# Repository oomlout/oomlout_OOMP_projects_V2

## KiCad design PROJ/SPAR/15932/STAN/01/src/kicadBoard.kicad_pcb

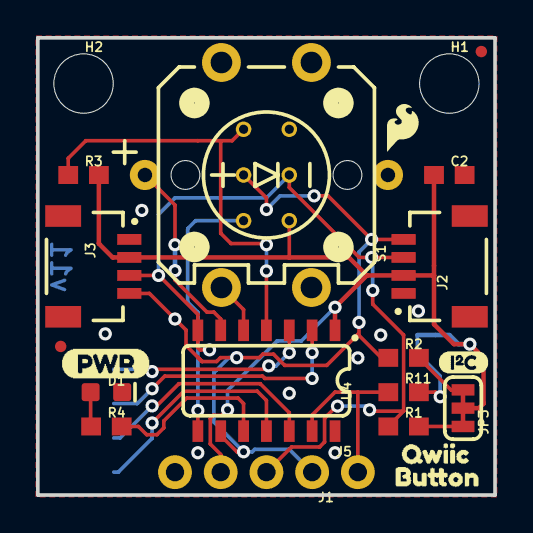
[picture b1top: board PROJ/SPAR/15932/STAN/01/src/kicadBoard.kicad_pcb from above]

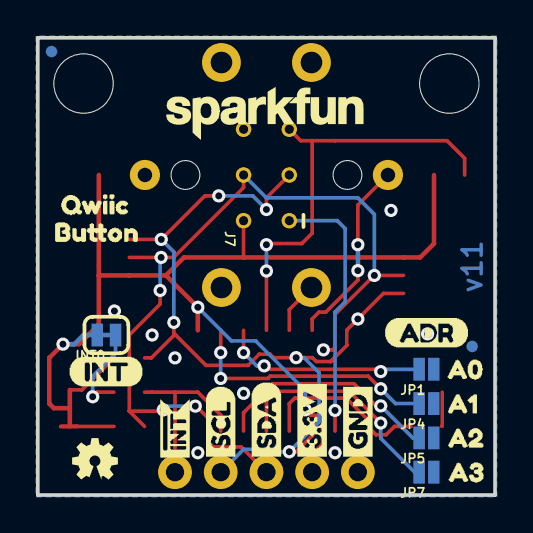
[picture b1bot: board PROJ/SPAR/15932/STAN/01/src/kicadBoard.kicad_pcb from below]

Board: 2 copper layers, 25.4 x 25.4 mm, 48 parts (23 on the bottom side), 18 nets.

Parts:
C2: 0.1uF; 0603
D1: RED; LED-0603
FRAME1: FRAME-LETTER; CREATIVE_COMMONS
H1, H2: STAND-OFF
INT0: JUMPER-SMT_2_NC_TRACE_SILK; SMT-JUMPER_2_NC_TRACE_SILK
J1: 1X04_NO_SILK
J2, J3: QWIIC_RIGHT_ANGLE; JST04_1MM_RA
J5: 1X01_NO_SILK
J7: ISP; 2X3_TEST_POINTS
JP1, JP4, JP5, JP7: JUMPER-SMT_2_NO_NO-SILK; SMT-JUMPER_2_NO_NO-SILK
JP2, JP6, JP8, JP9: FIDUCIALUFIDUCIAL; MICRO-FIDUCIAL
JP3: JUMPER-SMT_3_2-NC_TRACE_SILK; SMT-JUMPER_3_2-NC_TRACE_SILK
LOGO1: OSHW-LOGOMINI; OSHW-LOGO-MINI
LOGO2: REVISION
LOGO3: SFE_LOGO_NAME.1_INCH; SFE_LOGO_NAME_.1
LOGO4: SFE_LOGO_FLAME.1_INCH; SFE_LOGO_FLAME_.1
R1, R2: 2.2k; 0603
R3, R11: 10k; 0603
R4: 1k; 0603
S1: Button; TACTILE_SWITCH_LED_PTH_12MM
U4: ATTINY84-ARDUINO; SO14
U$1, U$2: BUTTON1
U$3: PWR-()-04
U$4: INT-()-04
U$5: SCL
U$6: SDA
U$7: 3.3V
U$8: GND
U$9: (ADR)
U$10: I_SUPER2_C-()-03
U$15: INT#-[_-04
U$16: A00
U$17: A11
U$19: A22
U$20, U$23: QWIIC0
U$21: A33

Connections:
3.3V: C2.1, INT0.2, J1.3, J2.2, J3.2, J7.2, JP3.2, R3.2, U4.1
ADR0: JP1.2, U4.3
ADR1: JP4.2, U4.2
ADR2: JP5.2, U4.12
ADR3: JP7.2, U4.11
GND: C2.2, D1.C, J1.4, J2.1, J3.1, J7.6, JP1.1, JP4.1, JP5.1, JP7.1, S1.2, S1.C, U4.14
INT_R: INT0.1, R11.2
LED: S1.A, U4.6
MISO: J7.1, U4.8
unnamed: D1.A, R4.1
SCL: J1.1, J2.4, J3.4, J7.3, R2.1, U4.9
SCL_PU1: JP3.1, R2.2
SDA: J1.2, J2.3, J3.3, J7.4, R1.1, U4.7
SDA_PU1: JP3.3, R1.2
STAT: R4.2, U4.10
SWITCH: S1.4, U4.5
~INT: J5.1, R11.1, U4.13
~RST: J7.5, R3.1, U4.4

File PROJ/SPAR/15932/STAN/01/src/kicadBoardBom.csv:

"Id";"Designator";"Package";"Quantity";"Designation";"Supplier and ref";
1;"H2,H1";"STAND-OFF";2;"STAND-OFF";;;
2;"D1";"LED-0603";1;"RED";;;
3;"J2,J3";"JST04_1MM_RA";2;"QWIIC_RIGHT_ANGLE";;;
4;"R4";"0603";1;"1k";;;
5;"U4";"SO14";1;"ATTINY84-ARDUINO";;;
6;"FRAME1";"CREATIVE_COMMONS";1;"FRAME-LETTER";;;
7;"R1,R2";"0603";2;"2.2k";;;
8;"R3,R11";"0603";2;"10k";;;
9;"J1";"1X04_NO_SILK";1;"";;;
10;"LOGO4";"SFE_LOGO_FLAME_.1";1;"SFE_LOGO_FLAME.1_INCH";;;
11;"U$23,U$20";"QWIIC0";2;"";;;
12;"U$1,U$2";"BUTTON1";2;"";;;
13;"U$3";"PWR-()-04";1;"";;;
14;"J5";"1X01_NO_SILK";1;"";;;
15;"JP9,JP8,JP2,JP6";"MICRO-FIDUCIAL";4;"FIDUCIALUFIDUCIAL";;;
16;"U$10";"I_SUPER2_C-()-03";1;"";;;
17;"C2";"0603";1;"0.1uF";;;
18;"S1";"TACTILE_SWITCH_LED_PTH_12MM";1;"Button";;;
19;"LOGO2";"REVISION";1;"REVISION";;;
20;"JP3";"SMT-JUMPER_3_2-NC_TRACE_SILK";1;"JUMPER-SMT_3_2-NC_TRACE_SILK";;;
21;"U$21";"A33";1;"";;;
22;"JP5,JP7,JP1,JP4";"SMT-JUMPER_2_NO_NO-SILK";4;"JUMPER-SMT_2_NO_NO-SILK";;;
23;"U$16";"A00";1;"";;;
24;"U$8";"GND";1;"";;;
25;"U$9";"(ADR)";1;"";;;
26;"J7";"2X3_TEST_POINTS";1;"ISP";;;
27;"U$6";"SDA";1;"";;;
28;"INT0";"SMT-JUMPER_2_NC_TRACE_SILK";1;"JUMPER-SMT_2_NC_TRACE_SILK";;;
29;"U$19";"A22";1;"";;;
30;"U$5";"SCL";1;"";;;
31;"LOGO1";"OSHW-LOGO-MINI";1;"OSHW-LOGOMINI";;;
32;"U$15";"INT#-[_-04";1;"";;;
33;"U$4";"INT-()-04";1;"";;;
34;"U$7";"3.3V";1;"";;;
35;"U$17";"A11";1;"";;;
36;"LOGO3";"SFE_LOGO_NAME_.1";1;"SFE_LOGO_NAME.1_INCH";;;

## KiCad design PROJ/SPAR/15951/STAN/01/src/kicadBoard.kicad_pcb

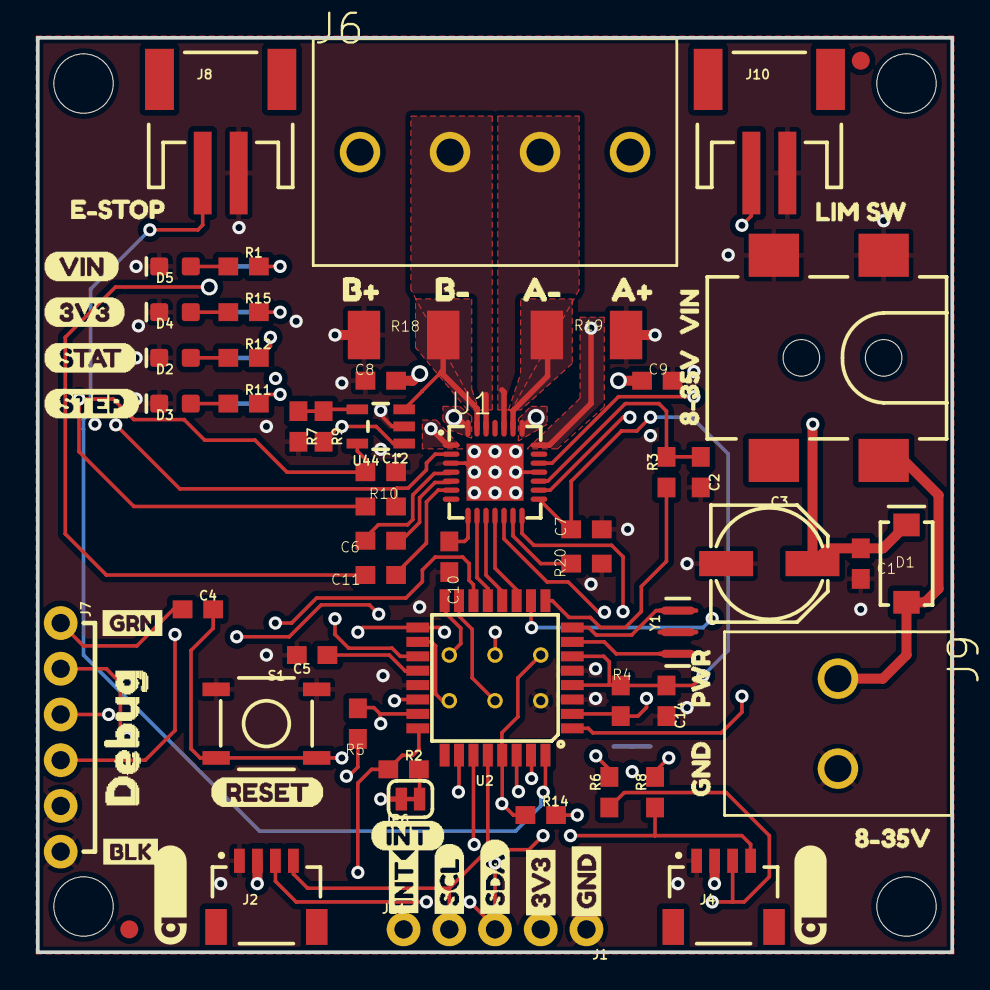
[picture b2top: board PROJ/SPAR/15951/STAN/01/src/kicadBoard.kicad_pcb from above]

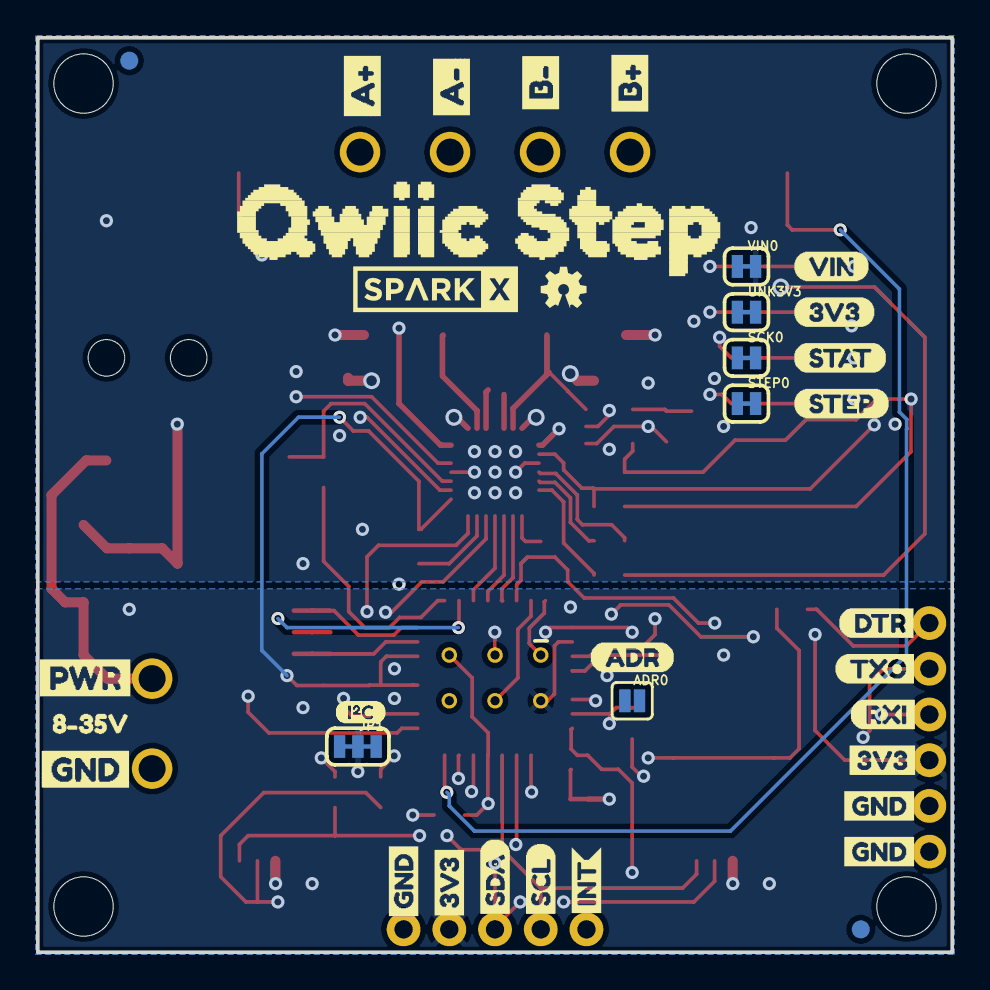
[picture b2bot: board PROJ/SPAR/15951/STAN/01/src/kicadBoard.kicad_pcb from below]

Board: 4 copper layers, 50.8 x 50.8 mm, 122 parts (37 on the bottom side), 54 nets.

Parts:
ADR0: ADR; SMT-JUMPER_2_NO_SILK
C1, C4, C5, C6, C7, C8, C9, C11, C12, C14: 0.1uF; 0603
C2: 1.0uF; 0603
C3: 47uF; PANASONIC_D
C10: 0.22uF; 0603
D1: 3A/40V/500mV; SMA-DIODE
D2: BLUE; LED-0603
D3: GREEN; LED-0603
D4: RED; LED-0603
D5: Yellow; LED-0603
FD1, FD2, FD3, FD4: FIDUCIAL1X2; FIDUCIAL-1X2
FRAME2: FRAME-LEDGER; CREATIVE_COMMONS
J1: PTH; 1X04_NO_SILK
J2, J4: Qwiic Right Angle; JST04_1MM_RA
J3: 5.5x2.1mm Barrel; POWER_JACK_SMD
J5: ISP; 2X3_TEST_POINTS
J6: LATCHTERMINAL-5MM-4
J7: 1X06_NO_SILK
J8, J10: JST-2-SMD
J9: LATCHTERMINAL-5MM-2
J11: 1X01_NO_SILK
JP1: SMT-JUMPER_3_2-NC_TRACE_SILK
JP6: INT; SMT-JUMPER_2_NC_TRACE_SILK
JP7, JP8, JP9, JP10: STAND-OFF
LOGO1: OSHW-LOGOMINI; OSHW-LOGO-MINI
R1, R2, R14: 10k; 0603
R3: 100k; 0603
R4, R5, R10, R20: 20k; 0603
R6, R8: 2.2k; 0603
R7, R15: 1k; 0603
R9: 22k; 0603
R11: 0; 0603
R12: 470; 0603
R18, R19: 0.11; 2010
S1: Tall Switch; TACTILE_SWITCH_SMD_5.2MM
SCK0: JUMPER-SMT_2_NC_TRACE_SILK; SMT-JUMPER_2_NC_TRACE_SILK
STEP0: JUMPER-SMT_2_NC_TRACE_SILK; SMT-JUMPER_2_NC_TRACE_SILK
U1: A4988ALT1; QFN-28-5MM
U2: ATMEGA328P_TQFP; TQFP32-08
U44: OPA344; SOT23-5
U$1: 3V30
U$2: 3V37
U$3: GND8
U$4: STAT5
U$5: SCL5
U$6: SDA6
U$7: STEP4
U$8: VIN3
U$9, U$29: QWIIC_5.5MM
U$10, U$11, U$40: 8#35V0
U$12: VIN1
U$13: STAT0
U$14: E#STOP2
U$15, U$16: I_SUPER2_C-()-03
U$17, U$45: 3V31
U$18: DTR4
U$19: DEBUG0
U$20: BLK2
U$21, U$22, U$44: GND0
U$23: LIM_SW3
U$24, U$30: INT4
U$25: ADR0
U$26: 3V35
U$27: RESET1
U$28: GRN1
U$31: GND6
U$32, U$54: A#2
U$33: SDA4
U$34: SCL3
U$35: RXI3
U$36, U$55: A#3
U$37: STEP2
U$38: VIN0
U$41: INT2
U$42: GND1
U$43: PWR0
U$46, U$57: B#4
U$47, U$58: B#5
U$48: TXO2
U$49: SPARKX-LOGO4; SPARKX-MEDIUM
U$53: PWR1
U$56: QWIIC_STEP0
UNK3V3: JUMPER-SMT_2_NC_TRACE_SILK; SMT-JUMPER_2_NC_TRACE_SILK
VIN0: JUMPER-SMT_2_NC_TRACE_SILK; SMT-JUMPER_2_NC_TRACE_SILK
Y1: 16MHz; RESONATOR-SMD-3.2X1.3

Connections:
3.3V: C7.1, C12.1, C14.1, J1.2, J2.2, J4.2, J5.2, J7.4, JP1.2, JP6.2, R4.2, R5.2, R10.2, R14.2, U1.15, U2.4, U2.6, U2.18, U44.5, UNK3V3.2
A49885_~RESET: R5.1, U1.12, U2.23
AMP_CUR_SENSE: R9.2, U2.19, U44.1
AREF: C5.1, U2.20
COILA+: J6.P$4, U1.21
COILA-: J6.P$3, U1.24
COILB+: J6.P$1, U1.1
COILB-: J6.P$2, U1.26
CURRENT_SENSE: R18.2, U1.27, U44.3
CUR_REF: C2.1, R3.2, U1.17
CUR_REF_PWM: R3.1, U2.9
DIR: U1.19, U2.10
DTR: C4.1, J7.1
GND: ADR0.2, C1.2, C2.2, C3.-, C5.2, C7.2, C8.2, C9.2, C10.2, C12.2, C14.2, D2.C, D3.C, D4.C, D5.C, J1.1, J2.1, J3.GND, J3.P$4, J4.1, J5.6, J7.5, J7.6, J8.2, J9.P$2, J10.2, R7.2, R18.1, R19.1, R20.2, S1.1, S1.2, U1.3, U1.18, U1.29, U2.3, U2.5, U2.21, U44.2, Y1.2
INT: J11.1, R2.1, U2.24
INT0: J8.1, U2.32
INT1: J10.1, U2.1
MISO: J5.1, U2.16
MOSI: J5.4, U2.15
MS1: U1.9, U2.13
MS2: U1.10, U2.12
MS3: U1.11, U2.11
unnamed: D3.A, R11.1
unnamed: R7.1, R9.1, U44.4
unnamed: R19.2, U1.23
unnamed: R1.2, VIN0.1
unnamed: JP6.1, R2.2
unnamed: ADR0.1, U2.22
unnamed: D1.A, J3.VIN0, J9.P$1
unnamed: C6.1, U1.4
unnamed: C6.2, U1.5
unnamed: D5.A, R1.1
unnamed: R11.2, STEP0.1
unnamed: D2.A, R12.1
unnamed: U2.7, Y1.1
unnamed: U2.8, Y1.3
unnamed: JP1.3, R6.2
unnamed: JP1.1, R8.2
unnamed: R12.2, SCK0.1
unnamed: R20.1, U1.13
unnamed: C10.1, U1.8
unnamed: C11.1, U1.6
unnamed: D4.A, R15.1
unnamed: R15.2, UNK3V3.1
RXI: J7.3, U2.30
SCK: J5.3, SCK0.2, U2.17
SCL: J1.4, J2.4, J4.4, R8.1, U2.28
SDA: J1.3, J2.3, J4.3, R6.1, U2.27
STEP: STEP0.2, U1.16, U2.26
TXO: J7.2, U2.31
VIN: C1.1, C3.+, C8.1, C9.1, C11.2, D1.C, U1.22, U1.28, VIN0.2
~ENABLE: R10.1, U1.2, U2.14
~RST: C4.2, J5.5, R14.1, S1.3, S1.4, U2.29
~SLEEP: R4.1, U1.14, U2.2

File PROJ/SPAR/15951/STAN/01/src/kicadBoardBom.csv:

"Id";"Designator";"Package";"Quantity";"Designation";"Supplier and ref";
1;"J9";"LATCHTERMINAL-5MM-2";1;"";;;
2;"U$46,U$57";"B#4";2;"";;;
3;"C7,C11,C5,C1,C12,C4,C8,C6,C9,C14";"0603";10;"0.1uF";;;
4;"U$8";"VIN3";1;"";;;
5;"R3";"0603";1;"100k";;;
6;"U$9,U$29";"QWIIC_5.5MM";2;"";;;
7;"R19,R18";"2010";2;"0.11";;;
8;"D3";"LED-0603";1;"GREEN";;;
9;"C2";"0603";1;"1.0uF";;;
10;"U$40,U$10,U$11";"8#35V0";3;"";;;
11;"R5,R4,R10,R20";"0603";4;"20k";;;
12;"FD4,FD1,FD3,FD2";"FIDUCIAL-1X2";4;"FIDUCIAL1X2";;;
13;"J8,J10";"JST-2-SMD";2;"";;;
14;"J6";"LATCHTERMINAL-5MM-4";1;"";;;
15;"R15,R7";"0603";2;"1k";;;
16;"U$7";"STEP4";1;"";;;
17;"U44";"SOT23-5";1;"OPA344";;;
18;"U$28";"GRN1";1;"";;;
19;"D4";"LED-0603";1;"RED";;;
20;"U$23";"LIM_SW3";1;"";;;
21;"U$24,U$30";"INT4";2;"";;;
22;"J11";"1X01_NO_SILK";1;"";;;
23;"J2,J4";"JST04_1MM_RA";2;"Qwiic Right Angle";;;
24;"U$14";"E#STOP2";1;"";;;
25;"D2";"LED-0603";1;"BLUE";;;
26;"D1";"SMA-DIODE";1;"3A/40V/500mV";;;
27;"U$32,U$54";"A#2";2;"";;;
28;"JP7,JP8,JP10,JP9";"STAND-OFF";4;"STAND-OFF";;;
29;"R11";"0603";1;"0";;;
30;"R14,R1,R2";"0603";3;"10k";;;
31;"U$19";"DEBUG0";1;"";;;
32;"U$47,U$58";"B#5";2;"";;;
33;"U$2";"3V37";1;"";;;
34;"U$42";"GND1";1;"";;;
35;"U1";"QFN-28-5MM";1;"A4988ALT1";;;
36;"U2";"TQFP32-08";1;"ATMEGA328P_TQFP";;;
37;"R6,R8";"0603";2;"2.2k";;;
38;"R9";"0603";1;"22k";;;
39;"U$12";"VIN1";1;"";;;
40;"C3";"PANASONIC_D";1;"47uF";;;
41;"U$4";"STAT5";1;"";;;
42;"U$43";"PWR0";1;"";;;
43;"J1";"1X04_NO_SILK";1;"PTH";;;
44;"C10";"0603";1;"0.22uF";;;
45;"U$1";"3V30";1;"";;;
46;"R12";"0603";1;"470";;;
47;"JP6";"SMT-JUMPER_2_NC_TRACE_SILK";1;"INT";;;
48;"U$36,U$55";"A#3";2;"";;;
49;"FRAME2";"CREATIVE_COMMONS";1;"FRAME-LEDGER";;;
50;"U$20";"BLK2";1;"";;;
51;"U$6";"SDA6";1;"";;;
52;"S1";"TACTILE_SWITCH_SMD_5.2MM";1;"Tall Switch";;;
53;"J3";"POWER_JACK_SMD";1;"5.5x2.1mm Barrel";;;
54;"Y1";"RESONATOR-SMD-3.2X1.3";1;"16MHz";;;
55;"U$5";"SCL5";1;"";;;
56;"U$3";"GND8";1;"";;;
57;"U$41";"INT2";1;"";;;
58;"J7";"1X06_NO_SILK";1;"";;;
59;"U$27";"RESET1";1;"";;;
60;"D5";"LED-0603";1;"Yellow";;;
61;"U$25";"ADR0";1;"";;;
62;"JP1";"SMT-JUMPER_3_2-NC_TRACE_SILK";1;"";;;
63;"SCK0,STEP0,VIN0,UNK3V3";"SMT-JUMPER_2_NC_TRACE_SILK";4;"JUMPER-SMT_2_NC_TRACE_SILK";;;
64;"U$38";"VIN0";1;"";;;
65;"U$13";"STAT0";1;"";;;
66;"U$18";"DTR4";1;"";;;
67;"U$45,U$17";"3V31";2;"";;;
68;"U$31";"GND6";1;"";;;
69;"U$26";"3V35";1;"";;;
70;"ADR0";"SMT-JUMPER_2_NO_SILK";1;"ADR";;;
71;"U$56";"QWIIC_STEP0";1;"";;;
72;"U$44,U$22,U$21";"GND0";3;"";;;
73;"U$48";"TXO2";1;"";;;
74;"U$49";"SPARKX-MEDIUM";1;"SPARKX-LOGO4";;;
75;"U$37";"STEP2";1;"";;;
76;"U$35";"RXI3";1;"";;;
77;"U$34";"SCL3";1;"";;;
78;"U$33";"SDA4";1;"";;;
79;"U$16,U$15";"I_SUPER2_C-()-03";2;"";;;
80;"LOGO1";"OSHW-LOGO-MINI";1;"OSHW-LOGOMINI";;;
81;"U$53";"PWR1";1;"";;;
82;"J5";"2X3_TEST_POINTS";1;"ISP";;;

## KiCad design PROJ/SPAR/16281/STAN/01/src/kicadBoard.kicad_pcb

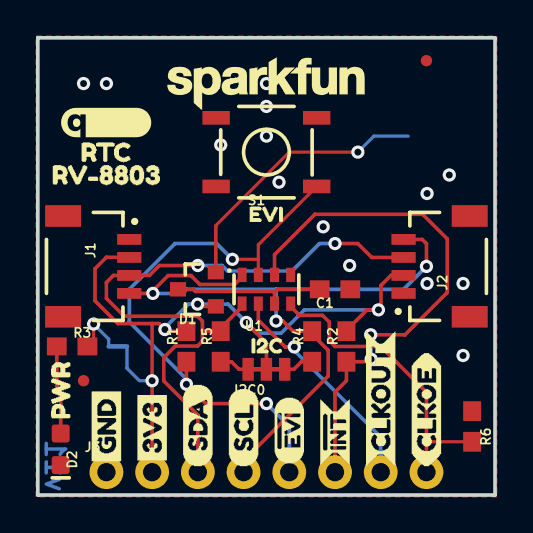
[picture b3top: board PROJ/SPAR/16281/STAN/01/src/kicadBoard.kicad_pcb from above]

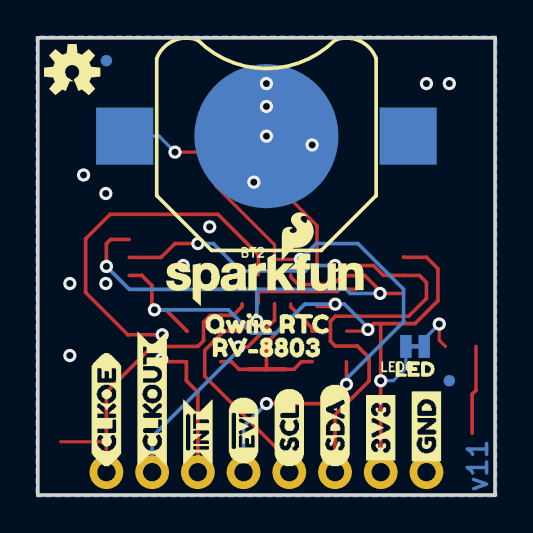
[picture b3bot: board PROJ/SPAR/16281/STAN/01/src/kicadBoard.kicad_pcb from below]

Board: 2 copper layers, 25.4 x 25.4 mm, 50 parts (17 on the bottom side), 14 nets.

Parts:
BT2: BATTCON_12MM
C1: 10nF; 0603
D1: BAS70-05; SOT23-3
D2: RED; LED-0603
FD1, FD2, FD3, FD4: FIDUCIALUFIDUCIAL; FIDUCIAL-MICRO
FRAME1: FRAME-LETTER; CREATIVE_COMMONS
I2C0: JUMPER-SMT_3_2-NC_TRACE_NO-SILK; SMT-JUMPER_3_2-NC_TRACE_NO-SILK
J1, J2: QWIIC; JST04_1MM_RA
J3: 1X08_NO_SILK
LED0: JUMPER-SMT_2_NC_TRACE_NO-SILK; SMT-JUMPER_2_NC_TRACE_NO-SILK
LOGO1: SFE_LOGO_NAME_FLAME.1_INCH; SFE_LOGO_NAME_FLAME_.1
LOGO2: OSHW-LOGOS; OSHW-LOGO-S
LOGO4: QWIIC_LOGO_5MM; QWIIC_5MM
LOGO5: SFE_LOGO_NAME.1_INCH; SFE_LOGO_NAME_.1
R1, R2, R6: 100k; 0603
R3: 1k; 0603
R4, R5: 4.7k; 0603
S1: MOMENTARY-SWITCH-SPST-SMD-5.2MM-TALL; TACTILE_SWITCH_SMD_5.2MM
U1: RV-8803; RV-3028
U$1, U$2: 3V31
U$3, U$4: GND0
U$5, U$6: SDA2
U$7, U$8: SCL3
U$9, U$10: #EVI2
U$11, U$12: CLKOUT6
U$13, U$14: CLKOE7
U$15, U$16: #INT5
U$17: PWR7
U$18: EVI1
U$19: I2C0
U$20: LED2
U$21: QWIIC_RTC0
U$22, U$24: _RV#88031
U$25: RTC0

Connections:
3.3V: D1.1, I2C0.2, J1.2, J2.2, J3.2, LED0.2, R1.2, R2.2
CLKOE: J3.8, R6.2, U1.4
CLKOUT: J3.7, U1.2
GND: BT2.GND, C1.1, D2.C, J1.1, J2.1, J3.1, R6.1, S1.3, U1.5
unnamed: C1.2, D1.3, U1.3
unnamed: D2.A, R3.1
unnamed: BT2.PWR@1, D1.2
unnamed: LED0.1, R3.2
unnamed: I2C0.3, R5.1
unnamed: I2C0.1, R4.1
SCL: J1.4, J2.4, J3.4, R4.2, U1.8
SDA: J1.3, J2.3, J3.3, R5.2, U1.1
~EVI: J3.5, R1.1, S1.1, U1.7
~INT: J3.6, R2.1, U1.6

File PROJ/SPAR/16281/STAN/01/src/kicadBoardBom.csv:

"Id";"Designator";"Package";"Quantity";"Designation";"Supplier and ref";
1;"U$7,U$8";"SCL3";2;"";;;
2;"U$17";"PWR7";1;"";;;
3;"S1";"TACTILE_SWITCH_SMD_5.2MM";1;"MOMENTARY-SWITCH-SPST-SMD-5.2MM-TALL";;;
4;"R5,R4";"0603";2;"4.7k";;;
5;"C1";"0603";1;"10nF";;;
6;"D1";"SOT23-3";1;"BAS70-05";;;
7;"FD1,FD3,FD2,FD4";"FIDUCIAL-MICRO";4;"FIDUCIALUFIDUCIAL";;;
8;"U$13,U$14";"CLKOE7";2;"";;;
9;"U$19";"I2C0";1;"";;;
10;"U$18";"EVI1";1;"";;;
11;"U$5,U$6";"SDA2";2;"";;;
12;"U1";"RV-3028";1;"RV-8803";;;
13;"U$15,U$16";"#INT5";2;"";;;
14;"R2,R6,R1";"0603";3;"100k";;;
15;"U$11,U$12";"CLKOUT6";2;"";;;
16;"U$24,U$22";"_RV#88031";2;"";;;
17;"LOGO4";"QWIIC_5MM";1;"QWIIC_LOGO_5MM";;;
18;"J2,J1";"JST04_1MM_RA";2;"QWIIC";;;
19;"U$9,U$10";"#EVI2";2;"";;;
20;"LOGO5";"SFE_LOGO_NAME_.1";1;"SFE_LOGO_NAME.1_INCH";;;
21;"R3";"0603";1;"1k";;;
22;"U$1,U$2";"3V31";2;"";;;
23;"U$25";"RTC0";1;"";;;
24;"D2";"LED-0603";1;"RED";;;
25;"I2C0";"SMT-JUMPER_3_2-NC_TRACE_NO-SILK";1;"JUMPER-SMT_3_2-NC_TRACE_NO-SILK";;;
26;"FRAME1";"CREATIVE_COMMONS";1;"FRAME-LETTER";;;
27;"J3";"1X08_NO_SILK";1;"";;;
28;"U$3,U$4";"GND0";2;"";;;
29;"LOGO2";"OSHW-LOGO-S";1;"OSHW-LOGOS";;;
30;"LED0";"SMT-JUMPER_2_NC_TRACE_NO-SILK";1;"JUMPER-SMT_2_NC_TRACE_NO-SILK";;;
31;"U$21";"QWIIC_RTC0";1;"";;;
32;"U$20";"LED2";1;"";;;
33;"BT2";"BATTCON_12MM";1;"";;;
34;"LOGO1";"SFE_LOGO_NAME_FLAME_.1";1;"SFE_LOGO_NAME_FLAME.1_INCH";;;

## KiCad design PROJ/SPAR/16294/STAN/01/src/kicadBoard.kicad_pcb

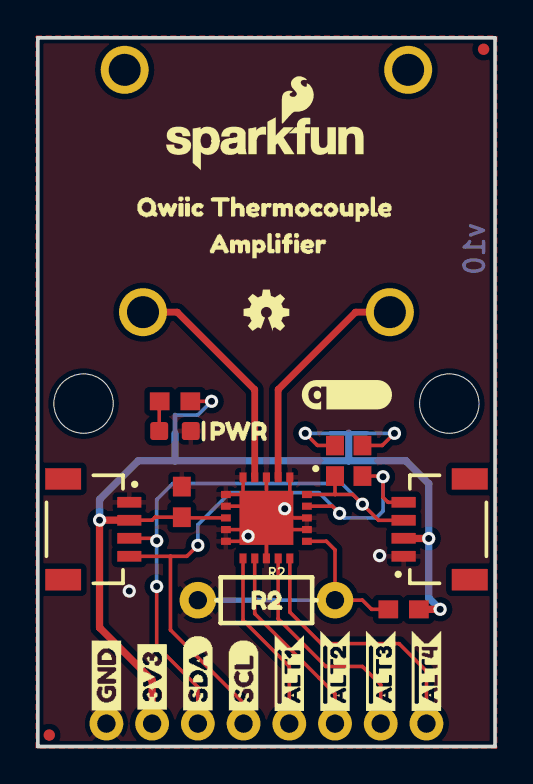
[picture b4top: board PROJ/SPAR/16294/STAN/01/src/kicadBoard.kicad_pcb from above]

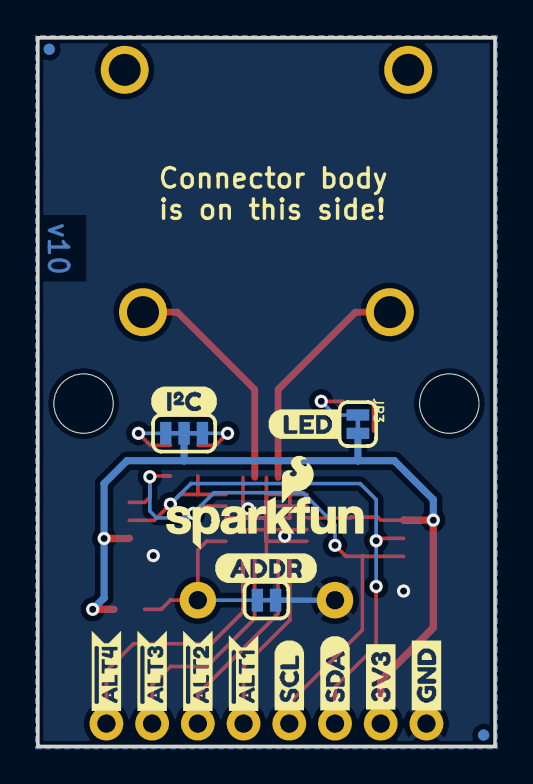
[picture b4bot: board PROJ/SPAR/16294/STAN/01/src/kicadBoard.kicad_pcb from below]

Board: 2 copper layers, 25.4 x 39.4 mm, 50 parts (18 on the bottom side), 15 nets.

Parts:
C1: 0.1uF; 0603
D1: RED; LED-0603
FD1, FD2, FD3, FD4: FIDUCIALUFIDUCIAL; FIDUCIAL-MICRO
FRAME1: FRAME-LETTER; CREATIVE_COMMONS
J1: PTH; 1X04_NO_SILK
J2, J3: QWIIC; JST04_1MM_RA
J4: 1X04_NO_SILK
J5: PCB_THERMOCOUPLE; PCC-SMP
JP1, JP3: SMT-JUMPER_2_NC_TRACE_SILK
JP2: I2C; SMT-JUMPER_3_2-NC_TRACE_SILK
JP8, JP9: STAND-OFF
LOGO1: OSHW-LOGOMINI; OSHW-LOGO-MINI
LOGO2: SFE_LOGO_NAME_FLAME.1_INCH; SFE_LOGO_NAME_FLAME_.1
LOGO3: QWIIC_LOGO_5MM; QWIIC_5MM
R1: 1k; 0603
R2: AXIAL-0.3-KIT
R3: 10k; 0603
R4, R5: 2.2k; 0603
U1: MCP9600-SMD; MQFN-20
U$1, U$5: #ALT30
U$2: R21
U$3, U$8: #ALT10
U$4, U$18: #ALT20
U$6: QWIIC_THERMOCOUPLE2
U$7, U$11: #ALT40
U$9, U$12: SCL-[)
U$10, U$23: GND-04
U$13, U$14: SDA-[)
U$15: PWR0
U$16, U$19: 3V31
U$17: SFE_LOGO_NAME_FLAME_.1
U$20: LED0
U$21: I_SUPER2_C-()-04
U$22: ADDR1
U$25: AMPLIFIER2

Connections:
3.3V: C1.1, J1.2, J2.2, J3.2, JP2.2, JP3.2, R3.2, U1.8
ADDR: JP1.1, R2.P$2, R3.1, U1.16
GND: C1.2, D1.C, J1.1, J2.1, J3.1, JP1.2, R2.P$1, U1.1, U1.3, U1.5, U1.6, U1.7, U1.9, U1.10, U1.13, U1.17, U1.18, U1.21
unnamed: D1.A, R1.2
unnamed: JP2.1, R5.2
unnamed: JP2.3, R4.2
unnamed: J5.+, U1.2
unnamed: J5.-, U1.4
unnamed: JP3.1, R1.1
SCL: J1.4, J2.4, J3.4, R5.1, U1.19
SDA: J1.3, J2.3, J3.3, R4.1, U1.20
~ALT1: J4.1, U1.11
~ALT2: J4.2, U1.12
~ALT3: J4.3, U1.14
~ALT4: J4.4, U1.15

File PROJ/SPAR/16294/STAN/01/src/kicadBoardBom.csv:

"Id";"Designator";"Package";"Quantity";"Designation";"Supplier and ref";
1;"U$17";"SFE_LOGO_NAME_FLAME_.1";1;"";;;
2;"FRAME1";"CREATIVE_COMMONS";1;"FRAME-LETTER";;;
3;"FD2,FD1,FD3,FD4";"FIDUCIAL-MICRO";4;"FIDUCIALUFIDUCIAL";;;
4;"U$2";"R21";1;"";;;
5;"D1";"LED-0603";1;"RED";;;
6;"R2";"AXIAL-0.3-KIT";1;" ";;;
7;"LOGO1";"OSHW-LOGO-MINI";1;"OSHW-LOGOMINI";;;
8;"R1";"0603";1;"1k";;;
9;"U$6";"QWIIC_THERMOCOUPLE2";1;"";;;
10;"U$15";"PWR0";1;"";;;
11;"U1";"MQFN-20";1;"MCP9600-SMD";;;
12;"U$25";"AMPLIFIER2";1;"";;;
13;"J2,J3";"JST04_1MM_RA";2;"QWIIC";;;
14;"J1";"1X04_NO_SILK";1;"PTH";;;
15;"U$18,U$4";"#ALT20";2;"";;;
16;"U$13,U$14";"SDA-[)";2;"";;;
17;"U$1,U$5";"#ALT30";2;"";;;
18;"U$12,U$9";"SCL-[)";2;"";;;
19;"U$11,U$7";"#ALT40";2;"";;;
20;"R3";"0603";1;"10k";;;
21;"JP8,JP9";"STAND-OFF";2;"STAND-OFF";;;
22;"U$8,U$3";"#ALT10";2;"";;;
23;"R4,R5";"0603";2;"2.2k";;;
24;"J4";"1X04_NO_SILK";1;"";;;
25;"LOGO3";"QWIIC_5MM";1;"QWIIC_LOGO_5MM";;;
26;"U$10,U$23";"GND-04";2;"";;;
27;"C1";"0603";1;"0.1uF";;;
28;"U$19,U$16";"3V31";2;"";;;
29;"JP2";"SMT-JUMPER_3_2-NC_TRACE_SILK";1;"I2C";;;
30;"LOGO2";"SFE_LOGO_NAME_FLAME_.1";1;"SFE_LOGO_NAME_FLAME.1_INCH";;;
31;"JP3,JP1";"SMT-JUMPER_2_NC_TRACE_SILK";2;"";;;
32;"U$22";"ADDR1";1;"";;;
33;"U$20";"LED0";1;"";;;
34;"J5";"PCC-SMP";1;"PCB_THERMOCOUPLE";;;
35;"U$21";"I_SUPER2_C-()-04";1;"";;;

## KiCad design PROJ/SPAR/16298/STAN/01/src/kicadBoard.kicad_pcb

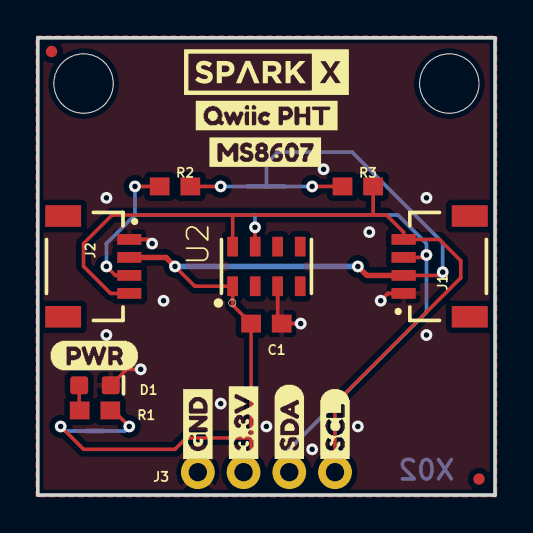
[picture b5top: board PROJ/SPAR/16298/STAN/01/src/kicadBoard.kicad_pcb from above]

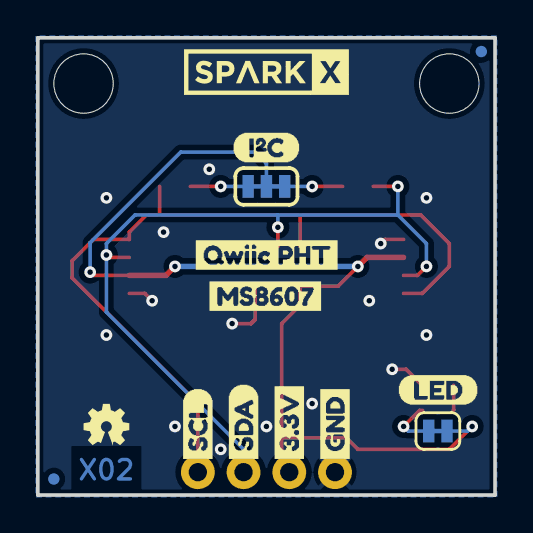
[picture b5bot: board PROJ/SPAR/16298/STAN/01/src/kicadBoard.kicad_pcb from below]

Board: 2 copper layers, 25.4 x 25.4 mm, 36 parts (14 on the bottom side), 8 nets.

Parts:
C1: 0.22uF; 0603
D1: RED; LED-0603
FRAME1: FRAME-LETTER; CREATIVE_COMMONS
I2C0: JUMPER-SMT_3_2-NC_TRACE_SILK; SMT-JUMPER_3_2-NC_TRACE_SILK
J1, J2: Qwiic Right Angle; JST04_1MM_RA
J3: PTH; 1X04_NO_SILK
JP1, JP2, JP5, JP6: FIDUCIALUFIDUCIAL; MICRO-FIDUCIAL
JP3, JP4: STAND-OFF
LED0: JUMPER-SMT_2_NC_TRACE_SILK; SMT-JUMPER_2_NC_TRACE_SILK
LOGO1: OSHW-LOGOMINI; OSHW-LOGO-MINI
R1: 1k; 0603
R2, R3: 2.2k; 0603
U2: MS8607-02BA01
U$1, U$2: SPARKX-LOGO4; SPARKX-MEDIUM
U$3, U$22: GND1
U$4, U$21: 3#3V2
U$5, U$27: SDA8
U$6, U$26: SCL9
U$9, U$12: QWIIC_PHT0
U$10: (PWR)
U$11: (I_SUPER2_C)
U$15, U$16: MS86070
U$17: LED0

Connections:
3.3V: C1.1, I2C0.2, J1.2, J2.2, J3.2, LED0.2, U2.1
GND: C1.2, D1.C, J1.1, J2.1, J3.1, U2.3
unnamed: I2C0.1, R3.2
unnamed: I2C0.3, R2.2
unnamed: D1.A, R1.1
unnamed: LED0.1, R1.2
SCL: J1.4, J2.4, J3.4, R3.1, U2.8
SDA: J1.3, J2.3, J3.3, R2.1, U2.7

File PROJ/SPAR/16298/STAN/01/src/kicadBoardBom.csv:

"Id";"Designator";"Package";"Quantity";"Designation";"Supplier and ref";
1;"U$22,U$3";"GND1";2;"";;;
2;"U$9,U$12";"QWIIC_PHT0";2;"";;;
3;"R1";"0603";1;"1k";;;
4;"U$27,U$5";"SDA8";2;"";;;
5;"U$10";"(PWR)";1;"";;;
6;"J2,J1";"JST04_1MM_RA";2;"Qwiic Right Angle";;;
7;"U$1,U$2";"SPARKX-MEDIUM";2;"SPARKX-LOGO4";;;
8;"R3,R2";"0603";2;"2.2k";;;
9;"JP4,JP3";"STAND-OFF";2;"STAND-OFF";;;
10;"U2";"MS8607-02BA01";1;"MS8607-02BA01";;;
11;"C1";"0603";1;"0.22uF";;;
12;"FRAME1";"CREATIVE_COMMONS";1;"FRAME-LETTER";;;
13;"D1";"LED-0603";1;"RED";;;
14;"U$15,U$16";"MS86070";2;"";;;
15;"J3";"1X04_NO_SILK";1;"PTH";;;
16;"JP2,JP6,JP5,JP1";"MICRO-FIDUCIAL";4;"FIDUCIALUFIDUCIAL";;;
17;"U$26,U$6";"SCL9";2;"";;;
18;"U$21,U$4";"3#3V2";2;"";;;
19;"LOGO1";"OSHW-LOGO-MINI";1;"OSHW-LOGOMINI";;;
20;"U$11";"(I_SUPER2_C)";1;"";;;
21;"U$17";"LED0";1;"";;;
22;"LED0";"SMT-JUMPER_2_NC_TRACE_SILK";1;"JUMPER-SMT_2_NC_TRACE_SILK";;;
23;"I2C0";"SMT-JUMPER_3_2-NC_TRACE_SILK";1;"JUMPER-SMT_3_2-NC_TRACE_SILK";;;

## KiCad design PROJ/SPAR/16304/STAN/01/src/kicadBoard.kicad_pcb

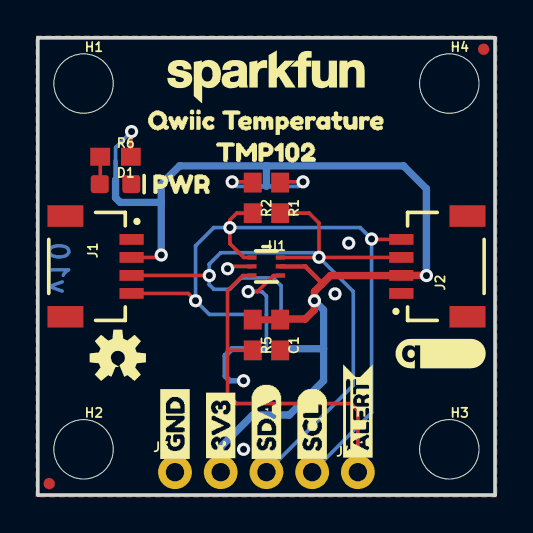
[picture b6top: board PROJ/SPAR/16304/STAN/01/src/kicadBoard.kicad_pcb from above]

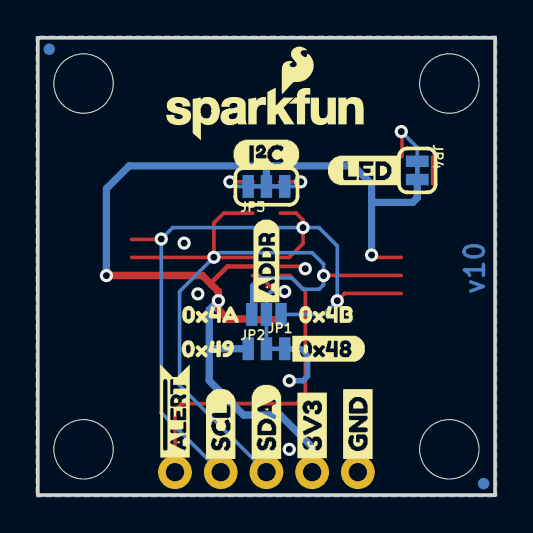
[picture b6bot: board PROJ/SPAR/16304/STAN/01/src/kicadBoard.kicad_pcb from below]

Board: 2 copper layers, 25.4 x 25.4 mm, 48 parts (19 on the bottom side), 10 nets.

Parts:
C1: 0.1uF; 0603
D1: RED; LED-0603
FD1, FD2, FD3, FD4: FIDUCIALUFIDUCIAL; FIDUCIAL-MICRO
FRAME1: FRAME-LETTER; CREATIVE_COMMONS
H1, H2, H3, H4: STAND-OFF
J1, J2: QWIIC; JST04_1MM_RA
J3: PTH; 1X04_NO_SILK
J4: 1X01_NO_SILK
JP1: SMT-JUMPER_3_1-NC_TRACE_NO-SILK
JP2: SMT-JUMPER_3_NO_NO-SILK
JP3: I2C; SMT-JUMPER_3_2-NC_TRACE_SILK
JP4: PWR; SMT-JUMPER_2_NC_TRACE_SILK
LOGO1: SFE_LOGO_NAME.1_INCH; SFE_LOGO_NAME_.1
LOGO2: QWIIC_LOGO_5MM; QWIIC_5MM
LOGO3: OSHW-LOGOS; OSHW-LOGO-S
R1, R2: 4.7k; 0603
R5: 10k; 0603
R6: 1k; 0603
U1: TMP102; SOT563
U$1, U$10: #ALERT8
U$2, U$9: SCL7
U$3, U$8: SDA6
U$4, U$7: 3V35
U$5, U$6: GND4
U$11: ADDR0
U$12: 0X481
U$13: 0X494
U$14: 0X4A2
U$15: 0X4B3
U$16: I#C0
U$17: LED0
U$18: QWIIC_TEMPERATURE0
U$19: TMP1022
U$20: PWR1
U$21: SFE_LOGO_NAME_FLAME_.1

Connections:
3.3V: C1.1, J1.2, J2.2, J3.2, JP1.1, JP3.2, JP4.2, R5.1, U1.5
ADDR: JP1.2, JP2.2, U1.4
GND: C1.2, D1.C, J1.1, J2.1, J3.1, JP1.3, U1.2
unnamed: JP3.3, R1.1
unnamed: JP3.1, R2.1
unnamed: D1.A, R6.1
unnamed: JP4.1, R6.2
SCL: J1.4, J2.4, J3.4, JP2.1, R2.2, U1.1
SDA: J1.3, J2.3, J3.3, JP2.3, R1.2, U1.6
~ALERT: J4.1, R5.2, U1.3

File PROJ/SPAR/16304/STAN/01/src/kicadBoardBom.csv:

"Id";"Designator";"Package";"Quantity";"Designation";"Supplier and ref";
1;"LOGO3";"OSHW-LOGO-S";1;"OSHW-LOGOS";;;
2;"U$1,U$10";"#ALERT8";2;"";;;
3;"U$5,U$6";"GND4";2;"";;;
4;"U$18";"QWIIC_TEMPERATURE0";1;"";;;
5;"U$2,U$9";"SCL7";2;"";;;
6;"J2,J1";"JST04_1MM_RA";2;"QWIIC";;;
7;"J4";"1X01_NO_SILK";1;"";;;
8;"H3,H4,H2,H1";"STAND-OFF";4;"STAND-OFF";;;
9;"LOGO2";"QWIIC_5MM";1;"QWIIC_LOGO_5MM";;;
10;"R6";"0603";1;"1k";;;
11;"C1";"0603";1;"0.1uF";;;
12;"U$4,U$7";"3V35";2;"";;;
13;"FD3,FD1,FD2,FD4";"FIDUCIAL-MICRO";4;"FIDUCIALUFIDUCIAL";;;
14;"R2,R1";"0603";2;"4.7k";;;
15;"R5";"0603";1;"10k";;;
16;"U$20";"PWR1";1;"";;;
17;"FRAME1";"CREATIVE_COMMONS";1;"FRAME-LETTER";;;
18;"U1";"SOT563";1;"TMP102";;;
19;"U$19";"TMP1022";1;"";;;
20;"D1";"LED-0603";1;"RED";;;
21;"LOGO1";"SFE_LOGO_NAME_.1";1;"SFE_LOGO_NAME.1_INCH";;;
22;"J3";"1X04_NO_SILK";1;"PTH";;;
23;"U$3,U$8";"SDA6";2;"";;;
24;"U$14";"0X4A2";1;"";;;
25;"U$17";"LED0";1;"";;;
26;"U$13";"0X494";1;"";;;
27;"JP3";"SMT-JUMPER_3_2-NC_TRACE_SILK";1;"I2C";;;
28;"U$16";"I#C0";1;"";;;
29;"JP2";"SMT-JUMPER_3_NO_NO-SILK";1;"";;;
30;"U$21";"SFE_LOGO_NAME_FLAME_.1";1;"";;;
31;"U$11";"ADDR0";1;"";;;
32;"U$12";"0X481";1;"";;;
33;"U$15";"0X4B3";1;"";;;
34;"JP1";"SMT-JUMPER_3_1-NC_TRACE_NO-SILK";1;"";;;
35;"JP4";"SMT-JUMPER_2_NC_TRACE_SILK";1;"PWR";;;

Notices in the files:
parts and their libraries:
HTTPS://CREATIVECOMMONS.ORG/LICENSES/BY-SA/4.0
RELEASED UNDER THE CREATIVE COMMONS ATTRIBUTION SHARE-ALIKE 4.0 LICENSE
